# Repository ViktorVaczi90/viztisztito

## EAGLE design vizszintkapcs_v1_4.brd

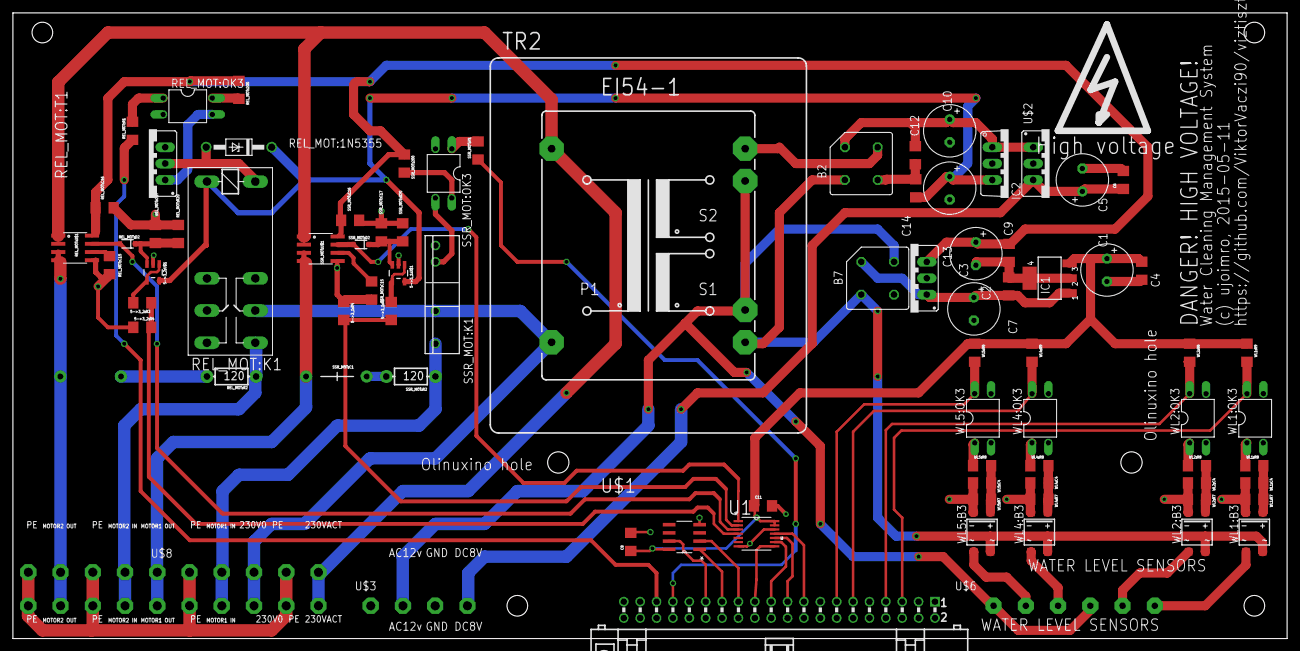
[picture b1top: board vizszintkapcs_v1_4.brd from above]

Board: 2 copper layers, 197.6 x 97.0 mm, 83 parts (1 on the bottom side), 61 nets.

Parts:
5->3_1:R3, 5->3_2:R3: 1.7; 1206
5->3_1:R4, 5->3_2:R4: 3.3; 1206
5->3_1:U$1, 5->3_2:U$1: OPA344; SOT23-5
7805: FAIRCHILD_LM7805CT; TO220S
B2, B7: 1KAB
C1, C2, C3, C5, C10, C13: 470uF; E3,5-8
C4, C6, C9, C14: 10nF; 1206
C7, C12: 10NF; 1206
C8, C11: 1uF; 1206
GPIO_CON1: BH40R
IC1: UA78M33DCY; SOT223
IC2: 7815TV; TO220V
REL_MOT:1N5355: ZPY; DO41Z10
REL_MOT:200: 2k; 1206
REL_MOT:C1: 0.1uF; CAP-PTH-LARGE
REL_MOT:C15: 1n; 1206
REL_MOT:C16: 0.1n; 1206
REL_MOT:C17: 10uF; 1206
REL_MOT:D2: 250mA/100V; SOD-323
REL_MOT:K1: G2R2
REL_MOT:OK3: PC817; DIL04
REL_MOT:R1: 400; 1206
REL_MOT:R2: 120; AXIAL-0.3-KIT
REL_MOT:R20: 0.1M; 1206
REL_MOT:T1: BDX53_STANDING; TO220S
REL_MOT:U$1: ACS712; SO08
SSR_MOT:200: 2k; 1206
SSR_MOT:C1: 0.1uF; CAP-PTH-LARGE
SSR_MOT:C15: 1n; 1206
SSR_MOT:C16: 0.1n; 1206
SSR_MOT:C17: 10uF; 1206
SSR_MOT:D2: 250mA/100V; SOD-323
SSR_MOT:K1: S102S02; S202S02
SSR_MOT:OK3: PC817; DIL04
SSR_MOT:R1: 400; 1206
SSR_MOT:R2: 120; AXIAL-0.3-KIT
SSR_MOT:R20: 0.1M; 1206
SSR_MOT:U$1: ACS712; SO08
TR2: EI54-2
U1: MCP3004-I/ST; SOP65P640X120-14N
U$1: TC77-5.0MOA; SOIC127P600X175-8N
U$2: STMICRO_L7808; TO220S
U$3: TERMINAL_BLOCK_4:METZ_AST1350404
U$6: TERMINAL_BLOCK_6:METZ_AST1350604
U$8: TERMINAL_BLOCK_10:METZ_AST0451004
WL1:B3, WL2:B3, WL4:B3, WL5:B3: MB6S; SOIC-4
WL1:C4, WL2:C4, WL4:C4, WL5:C4: 10uF; 1206
WL1:OK3, WL2:OK3, WL4:OK3, WL5:OK3: PC817; DIL04
WL1:R7, WL2:R7, WL4:R7, WL5:R7: 20k; 1206
WL1:R8, WL1:R9, WL2:R8, WL2:R9, WL4:R8, WL4:R9, WL5:R8, WL5:R9: 2k; 1206

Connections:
1_WATER_IN: U$6.P$1, WL1:B3.~1
2_WATER_IN: U$6.P$2, WL2:B3.~1
4_WATER_IN: U$6.P$4, WL4:B3.~1
5->3_1:N$1: 5->3_1:R3.2, 5->3_1:U$1.1, 5->3_1:U$1.4
5->3_2:N$1: 5->3_2:R3.2, 5->3_2:U$1.1, 5->3_2:U$1.4
5_WATER_IN: U$6.P$5, WL5:B3.~1
230V0: REL_MOT:K1.P1, SSR_MOT:K1.2, TR2.7, U$8.P$3@1, U$8.P$3@2
230VPHASE: REL_MOT:U$1.1, REL_MOT:U$1.2, SSR_MOT:U$1.1, SSR_MOT:U$1.2, TR2.1, U$8.P$1@1, U$8.P$1@2
!SPI1_CS: GPIO_CON1.23, U1.8
!SPI2_CS: GPIO_CON1.29, U$1.7
AC12V: B7.AC1, TR2.9, TR2.13, U$3.P$2, U$6.P$3, U$6.P$6
AC24V: B2.AC1, TR2.14
COMMON_EARTH: U$8.P$2@1, U$8.P$2@2, U$8.P$5@1, U$8.P$5@2, U$8.P$8@1, U$8.P$8@2, U$8.P$10@1, U$8.P$10@2
DC3.3V: C1.+, C4.1, C8.1, C11.1, IC1.3, U1.13, U1.14, U$1.8, WL1:R9.1, WL2:R9.1, WL4:R9.1, WL5:R9.1
DC5V: 7805.3, C3.+, C9.1, REL_MOT:200.1, REL_MOT:C16.1, REL_MOT:U$1.8, SSR_MOT:200.1, SSR_MOT:C16.1, SSR_MOT:U$1.8
DC8V: C5.+, C6.1, U$2.3, U$3.P$4
DC15V: 5->3_1:U$1.5, 5->3_2:U$1.5, C13.+, C14.1, IC2.3, REL_MOT:1N5355.C, REL_MOT:K1.1
GND: 5->3_1:R4.1, 5->3_1:U$1.2, 5->3_2:R4.1, 5->3_2:U$1.2, 7805.2, B2.-, B7.-, C1.-, C2.-, C3.-, C4.2, C5.-, C6.2, C7.2, C8.2, C9.2, C10.-, C11.2, C12.2, C13.-, C14.2, GPIO_CON1.2, IC1.2, IC1.4, IC2.2, REL_MOT:C15.2, REL_MOT:C16.2, REL_MOT:C17.2, REL_MOT:OK3.2, REL_MOT:R20.2, REL_MOT:T1.3, REL_MOT:U$1.5, SSR_MOT:C15.2, SSR_MOT:C16.2, SSR_MOT:C17.2, SSR_MOT:K1.4, SSR_MOT:OK3.2, SSR_MOT:R20.2, SSR_MOT:U$1.5, U1.7, U1.12, U$1.4, U$2.2, U$3.P$3, WL1:B3.-, WL1:C4.2, WL1:OK3.2, WL1:OK3.3, WL1:R7.1, WL2:B3.-, WL2:C4.2, WL2:OK3.2, WL2:OK3.3, WL2:R7.1, WL4:B3.-, WL4:C4.2, WL4:OK3.2, WL4:OK3.3, WL4:R7.1, WL5:B3.-, WL5:C4.2, WL5:OK3.2, WL5:OK3.3, WL5:R7.1
MOTOR_DIRECT_1: SSR_MOT:D2.A, SSR_MOT:U$1.7, U1.1
MOTOR_DIRECT_2: REL_MOT:D2.A, REL_MOT:U$1.7, U1.3
MOTOR_IN: SSR_MOT:K1.1, SSR_MOT:R2.P$1, U$8.P$4@1, U$8.P$4@2
MOTOR_IN_2: REL_MOT:K1.S1, REL_MOT:R2.P$1, U$8.P$7@1, U$8.P$7@2
MOTOR_OUT_1: SSR_MOT:C1.1, SSR_MOT:U$1.3, SSR_MOT:U$1.4, U$8.P$6@1, U$8.P$6@2
MOTOR_OUT_2: REL_MOT:C1.1, REL_MOT:U$1.3, REL_MOT:U$1.4, U$8.P$9@1, U$8.P$9@2
MOTOR_SENSE_1: 5->3_1:U$1.3, SSR_MOT:C17.1, SSR_MOT:D2.C, SSR_MOT:R20.1
MOTOR_SENSE_2: 5->3_2:U$1.3, REL_MOT:C17.1, REL_MOT:D2.C, REL_MOT:R20.1
P1.3: GPIO_CON1.7, WL2:OK3.4, WL2:R9.2
P1.5: GPIO_CON1.11, WL4:OK3.4, WL4:R9.2
P1.6: GPIO_CON1.33, SSR_MOT:R1.1
P2.4: GPIO_CON1.13, WL5:OK3.4, WL5:R9.2
P2.7: GPIO_CON1.35, REL_MOT:R1.1
P4.3: GPIO_CON1.5, WL1:OK3.4, WL1:R9.2
P6.0: 5->3_2:R3.1, 5->3_2:R4.2, U1.4
P6.1: 5->3_1:R3.1, 5->3_1:R4.2, U1.2
REC12V: 7805.1, B7.+, C2.+, C7.1, IC1.1
REC24V: B2.+, C10.+, C12.1, IC2.1, U$2.1
REL_MOT:N$1: REL_MOT:C1.2, REL_MOT:R2.P$2
REL_MOT:N$3: REL_MOT:200.2, REL_MOT:OK3.4
REL_MOT:N$4: REL_MOT:OK3.3, REL_MOT:T1.1
REL_MOT:N$10: REL_MOT:1N5355.A, REL_MOT:K1.2, REL_MOT:T1.2
REL_MOT:N$13: REL_MOT:OK3.1, REL_MOT:R1.2
REL_MOT:N$26: REL_MOT:C15.1, REL_MOT:U$1.6
SPI1_CLK: GPIO_CON1.17, U1.11
SPI1_MISO: GPIO_CON1.19, U1.10
SPI1_MOSI: GPIO_CON1.21, U1.9
SPI2_CLK: GPIO_CON1.25, U$1.2
SPI2_MISO: GPIO_CON1.27, U$1.1
SSR_MOT:N$1: SSR_MOT:C1.2, SSR_MOT:R2.P$2
SSR_MOT:N$3: SSR_MOT:200.2, SSR_MOT:OK3.4
SSR_MOT:N$4: SSR_MOT:K1.3, SSR_MOT:OK3.3
SSR_MOT:N$13: SSR_MOT:OK3.1, SSR_MOT:R1.2
SSR_MOT:N$26: SSR_MOT:C15.1, SSR_MOT:U$1.6
TRANS_OUT: B2.AC2, B7.AC2, TR2.8, WL1:B3.~2, WL2:B3.~2, WL4:B3.~2, WL5:B3.~2
WL1:N$12: WL1:B3.+, WL1:C4.1, WL1:R7.2, WL1:R8.2
WL1:N$13: WL1:OK3.1, WL1:R8.1
WL2:N$12: WL2:B3.+, WL2:C4.1, WL2:R7.2, WL2:R8.2
WL2:N$13: WL2:OK3.1, WL2:R8.1
WL4:N$12: WL4:B3.+, WL4:C4.1, WL4:R7.2, WL4:R8.2
WL4:N$13: WL4:OK3.1, WL4:R8.1
WL5:N$12: WL5:B3.+, WL5:C4.1, WL5:R7.2, WL5:R8.2
WL5:N$13: WL5:OK3.1, WL5:R8.1

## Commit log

2015-04-27 new version with gpios
2015-05-10 without MCU
2015-05-10 new GND text
2015-05-12 smaller version with danger sign and good holes
2015-07-07 save
2015-07-07 only 4 water level sensor on one board
2015-07-13 3.3v spi levels

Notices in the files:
parts and their libraries:
SparkFun-Passives: Licensing: Creative Commons ShareAlike 4.0 International - https://creativecommons.org/licenses/by-sa/4.0
